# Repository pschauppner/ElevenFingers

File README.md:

# ElevenFingers
An ergonomic split keyboard

## Notes/assumptions for this build
Encoder will be swapped in software (vice having a reverse footprint)
Most components are flipped for right side, LEDs are flipped AND rotated 180 degrees so that routes with vias can be more direct

## Issues and planned work
- Bluetooth is tempermental with pull down resistors - no longer needed for my current setup - plan to remove
- Source code has to get modified for flashing left half and right half - not great
- some software layout issues (no semi colon, tilde, grave, function keys...) - could really expand on use of layers
- OLED can be more helpful
- I don't like the sound of clicky keys - plan to switch to tactile
- hotswap sockets were a bad idea - they made connections less reliable (and I'm not a big keyswapper anyway)
- Next: case + PCB, better wires
- a power switch, and/or a reset button might be nice

## Project Navigation

### keyboard-layout-editor
This folder contains the json for uploading in the 'Raw Data' tab of [keyboard-layout-editor.com](http://www.keyboard-layout-editor.com/)
It's rotated right because it was easier for dealing with a columnar stagger this way (keyboard-layout-editor syntax is row-based, assuming each "row" is at the same vertical offset).

### qmk_firmware/keyboards/ElevenFingers
Contains the source code that would go under 'keyboards' in the qmk_firmware root directory (https://github.com/qmk/qmk_firmware)

Note - my idea is that any customizations to qmk will be added here with a script to copy it into the qmk repository.  (Why does QMK host so many individual keyboard source files?)

### fabrication
This keyboard is currently a cardboard prototype.  The svg was used as a template to cutout squares in a piece of cardboard.  In the future this will contain drawings for case and mounting plates.  Note I used http://builder.swillkb.com/ with the MX switch type (and otherwise default settings) to generate this SVG.

### circuitry
This keyboard was handwired.  This folder contains notes and pictures of the wiring.  In the future, this will contain PCB design files.

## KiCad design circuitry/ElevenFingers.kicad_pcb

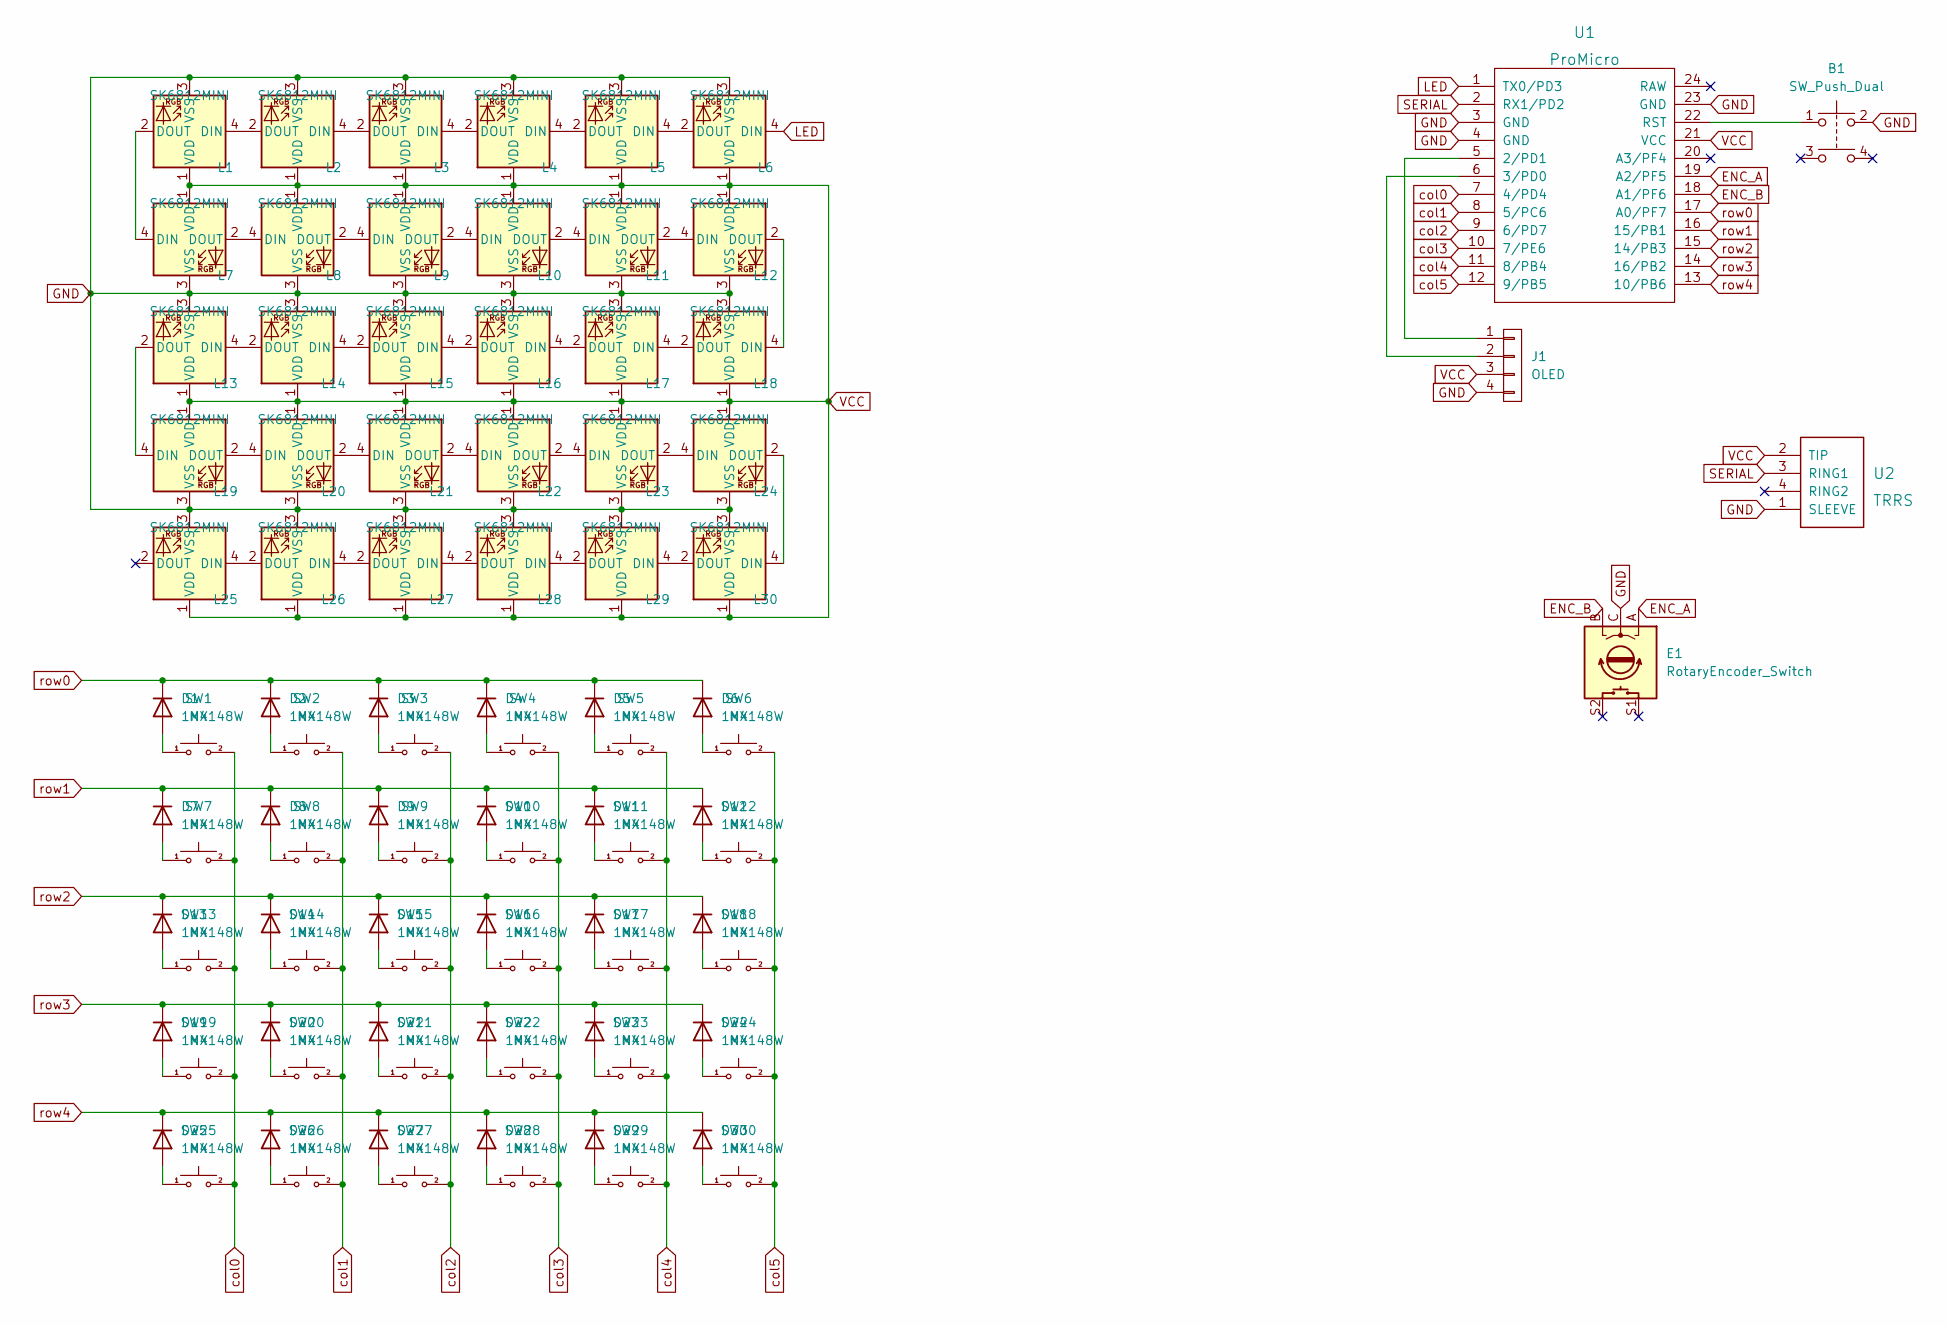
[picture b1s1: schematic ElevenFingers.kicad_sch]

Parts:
B1: SW_Push_Dual; Arduino_Pushbutton
D1, D2, D3, D4, D5, D6, D7, D8, D9, D10, D11, D12, D13, D14, D15, D16, D17, D18, D19, D20, D21, D22, D23, D24, D25, D26, D27, D28, D29, D30: 1N4148W; D_SOD-123
E1: RotaryEncoder_Switch; RotaryEncoder_EC11
J1: OLED; OLED_4Pin
L1, L2, L3, L4, L5, L6, L7, L8, L9, L10, L11, L12, L13, L14, L15, L16, L17, L18, L19, L20, L21, L22, L23, L24, L25, L26, L27, L28, L29, L30: SK6812MINI; LED_SK6812MINI_PLCC4_3.5x3.5mm_P1.75mm
SW1, SW2, SW3, SW4, SW5, SW6, SW7, SW8, SW9, SW10, SW11, SW12, SW13, SW14, SW15, SW16, SW17, SW18, SW19, SW20, SW21, SW22, SW23, SW24, SW25, SW26, SW27, SW28, SW29, SW30: MX; SW_Cherry_MX_1.00u_PCB
U1: ProMicro
U2: TRRS; TRRS-PJ-320A

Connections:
ENC_A: E1.A, U1.19 (A2/PF5)
ENC_B: E1.B, U1.18 (A1/PF6)
GND: B1.2, E1.C, J1.4, L1.3 (VSS), L2.3 (VSS), L3.3 (VSS), L4.3 (VSS), L5.3 (VSS), L6.3 (VSS), L7.3 (VSS), L8.3 (VSS), L9.3 (VSS), L10.3 (VSS), L11.3 (VSS), L12.3 (VSS), L13.3 (VSS), L14.3 (VSS), L15.3 (VSS), L16.3 (VSS), L17.3 (VSS), L18.3 (VSS), L19.3 (VSS), L20.3 (VSS), L21.3 (VSS), L22.3 (VSS), L23.3 (VSS), L24.3 (VSS), L25.3 (VSS), L26.3 (VSS), L27.3 (VSS), L28.3 (VSS), L29.3 (VSS), L30.3 (VSS), U1.3 (GND), U1.4 (GND), U1.23 (GND), U2.1 (SLEEVE)
LED: L6.4 (DIN), U1.1 (TX0/PD3)
unnamed: B1.1, U1.22 (RST)
unnamed: D1.2 (A), SW1.1
unnamed: D2.2 (A), SW2.1
unnamed: D3.2 (A), SW3.1
unnamed: D4.2 (A), SW4.1
unnamed: D5.2 (A), SW5.1
unnamed: D6.2 (A), SW6.1
unnamed: D7.2 (A), SW7.1
unnamed: D8.2 (A), SW8.1
unnamed: D9.2 (A), SW9.1
unnamed: D10.2 (A), SW10.1
unnamed: D11.2 (A), SW11.1
unnamed: D12.2 (A), SW12.1
unnamed: D13.2 (A), SW13.1
unnamed: D14.2 (A), SW14.1
unnamed: D15.2 (A), SW15.1
unnamed: D16.2 (A), SW16.1
unnamed: D17.2 (A), SW17.1
unnamed: D18.2 (A), SW18.1
unnamed: D19.2 (A), SW19.1
unnamed: D20.2 (A), SW20.1
unnamed: D21.2 (A), SW21.1
unnamed: D22.2 (A), SW22.1
unnamed: D23.2 (A), SW23.1
unnamed: D24.2 (A), SW24.1
unnamed: D25.2 (A), SW25.1
unnamed: D26.2 (A), SW26.1
unnamed: D27.2 (A), SW27.1
unnamed: D28.2 (A), SW28.1
unnamed: D29.2 (A), SW29.1
unnamed: D30.2 (A), SW30.1
unnamed: J1.1, U1.5 (2/PD1)
unnamed: J1.2, U1.6 (3/PD0)
unnamed: L1.2 (DOUT), L7.4 (DIN)
unnamed: L1.4 (DIN), L2.2 (DOUT)
unnamed: L2.4 (DIN), L3.2 (DOUT)
unnamed: L3.4 (DIN), L4.2 (DOUT)
unnamed: L4.4 (DIN), L5.2 (DOUT)
unnamed: L5.4 (DIN), L6.2 (DOUT)
unnamed: L7.2 (DOUT), L8.4 (DIN)
unnamed: L8.2 (DOUT), L9.4 (DIN)
unnamed: L10.2 (DOUT), L11.4 (DIN)
unnamed: L9.2 (DOUT), L10.4 (DIN)
unnamed: L11.2 (DOUT), L12.4 (DIN)
unnamed: L12.2 (DOUT), L18.4 (DIN)
unnamed: L13.2 (DOUT), L19.4 (DIN)
unnamed: L13.4 (DIN), L14.2 (DOUT)
unnamed: L14.4 (DIN), L15.2 (DOUT)
unnamed: L15.4 (DIN), L16.2 (DOUT)
unnamed: L16.4 (DIN), L17.2 (DOUT)
unnamed: L17.4 (DIN), L18.2 (DOUT)
unnamed: L19.2 (DOUT), L20.4 (DIN)
unnamed: L20.2 (DOUT), L21.4 (DIN)
unnamed: L21.2 (DOUT), L22.4 (DIN)
unnamed: L22.2 (DOUT), L23.4 (DIN)
unnamed: L23.2 (DOUT), L24.4 (DIN)
unnamed: L24.2 (DOUT), L30.4 (DIN)
unnamed: L25.4 (DIN), L26.2 (DOUT)
unnamed: L26.4 (DIN), L27.2 (DOUT)
unnamed: L27.4 (DIN), L28.2 (DOUT)
unnamed: L28.4 (DIN), L29.2 (DOUT)
unnamed: L29.4 (DIN), L30.2 (DOUT)
SERIAL: U1.2 (RX1/PD2), U2.3 (RING1)
VCC: J1.3, L1.1 (VDD), L2.1 (VDD), L3.1 (VDD), L4.1 (VDD), L5.1 (VDD), L6.1 (VDD), L7.1 (VDD), L8.1 (VDD), L9.1 (VDD), L10.1 (VDD), L11.1 (VDD), L12.1 (VDD), L13.1 (VDD), L14.1 (VDD), L15.1 (VDD), L16.1 (VDD), L17.1 (VDD), L18.1 (VDD), L19.1 (VDD), L20.1 (VDD), L21.1 (VDD), L22.1 (VDD), L23.1 (VDD), L24.1 (VDD), L25.1 (VDD), L26.1 (VDD), L27.1 (VDD), L28.1 (VDD), L29.1 (VDD), L30.1 (VDD), U1.21 (VCC), U2.2 (TIP)
col0: SW1.2, SW7.2, SW13.2, SW19.2, SW25.2, U1.7 (4/PD4)
col1: SW2.2, SW8.2, SW14.2, SW20.2, SW26.2, U1.8 (5/PC6)
col2: SW3.2, SW9.2, SW15.2, SW21.2, SW27.2, U1.9 (6/PD7)
col3: SW4.2, SW10.2, SW16.2, SW22.2, SW28.2, U1.10 (7/PE6)
col4: SW5.2, SW11.2, SW17.2, SW23.2, SW29.2, U1.11 (8/PB4)
col5: SW6.2, SW12.2, SW18.2, SW24.2, SW30.2, U1.12 (9/PB5)
row0: D1.1 (K), D2.1 (K), D3.1 (K), D4.1 (K), D5.1 (K), D6.1 (K), U1.17 (A0/PF7)
row1: D7.1 (K), D8.1 (K), D9.1 (K), D10.1 (K), D11.1 (K), D12.1 (K), U1.16 (15/PB1)
row2: D13.1 (K), D14.1 (K), D15.1 (K), D16.1 (K), D17.1 (K), D18.1 (K), U1.15 (14/PB3)
row3: D19.1 (K), D20.1 (K), D21.1 (K), D22.1 (K), D23.1 (K), D24.1 (K), U1.14 (16/PB2)
row4: D25.1 (K), D26.1 (K), D27.1 (K), D28.1 (K), D29.1 (K), D30.1 (K), U1.13 (10/PB6)

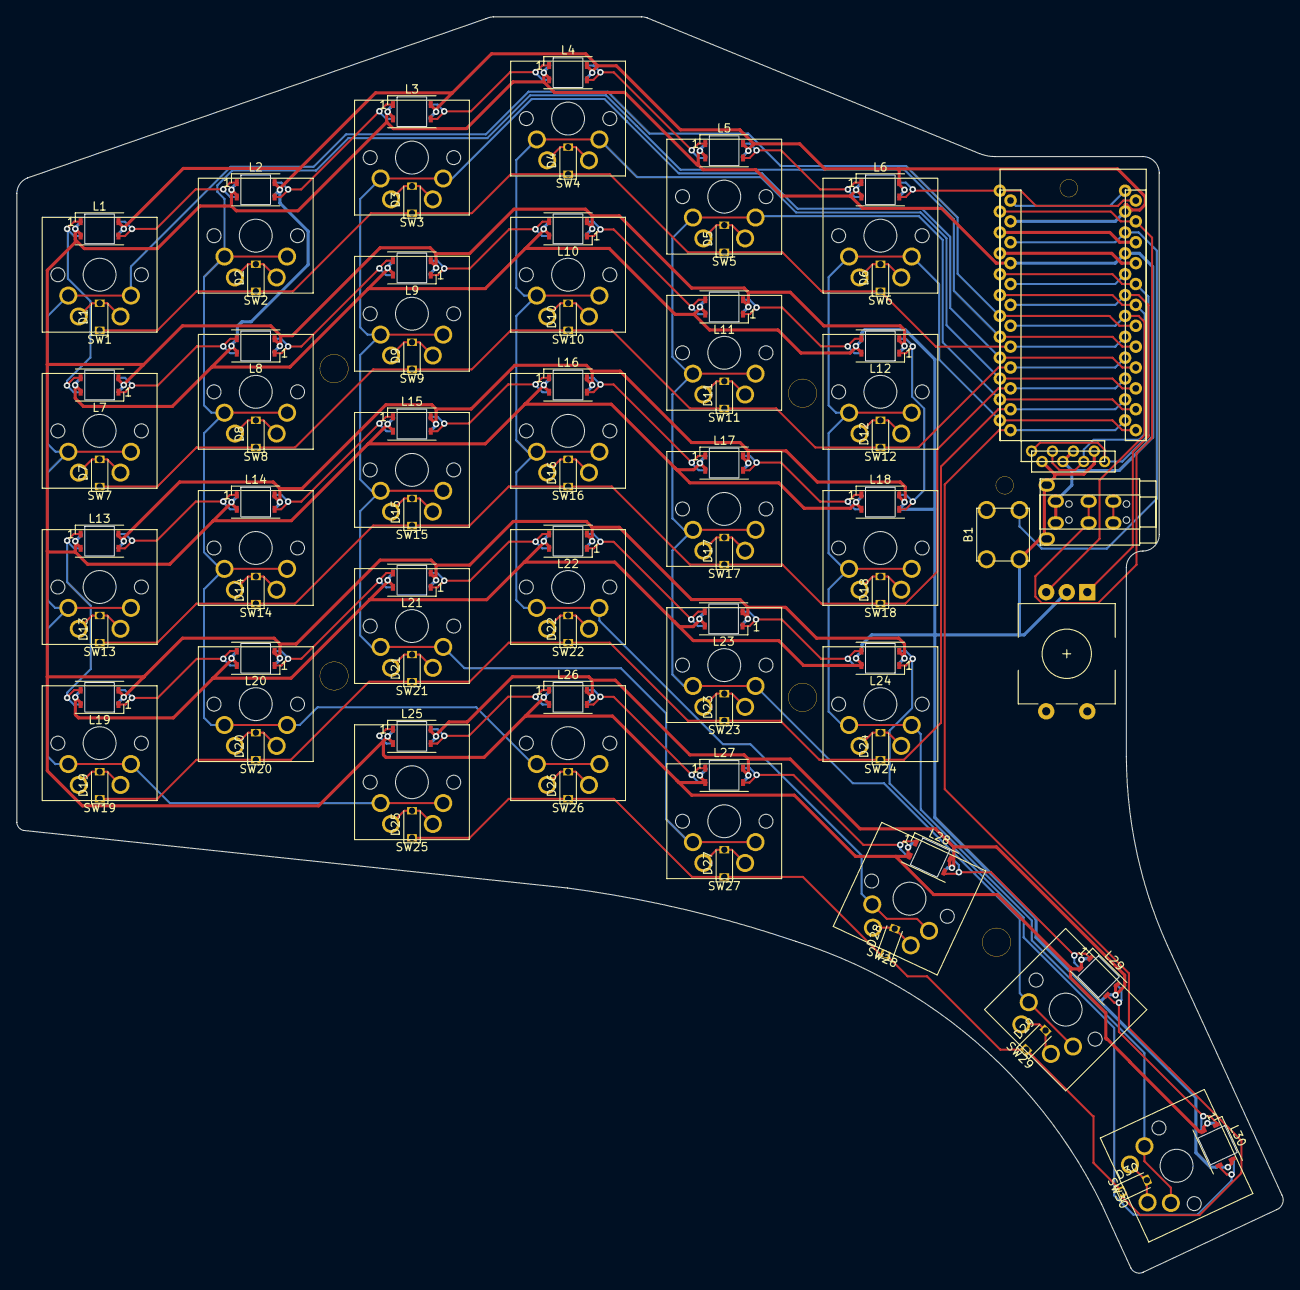
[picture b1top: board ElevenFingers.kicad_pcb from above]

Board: 2 copper layers, 154.1 x 152.8 mm, 95 parts (0 on the bottom side), 79 nets.

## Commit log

2022-06-17 adding layout, svg, parts, qmk source
2022-06-17 fixed folder structure to match qmk_firmware
2022-06-21 complete prototype board
2022-06-21 moved row0-4 and col0-5 pins
2022-06-24 finished schematic, customized footprints, organized pcb
2022-06-24 keys all placed, 1 led placed, no tracing yet
2022-06-25 started adding tracing
2022-06-25 all components traced internally, not yet connected
2022-06-25 routed rows
2022-06-25 routed columns
2022-06-25 rotated leds on alternating rows
2022-06-25 routed data for led rows (have not connected rows)
2022-06-25 routed rows and cols to ProMicro
2022-06-25 pwr and gnd routed for leds, (not to promicro, and not across rows)
2022-06-26 completed tracing?
2022-06-26 finished tracing and error checking
2022-06-27 tightened horizontal spacing of components
2022-07-08 completed plate layers and edge cuts
2022-07-10 changed pcb holes to NPTH, mechanical, generated case dxf files
2022-08-17 keyboard working in qmk
